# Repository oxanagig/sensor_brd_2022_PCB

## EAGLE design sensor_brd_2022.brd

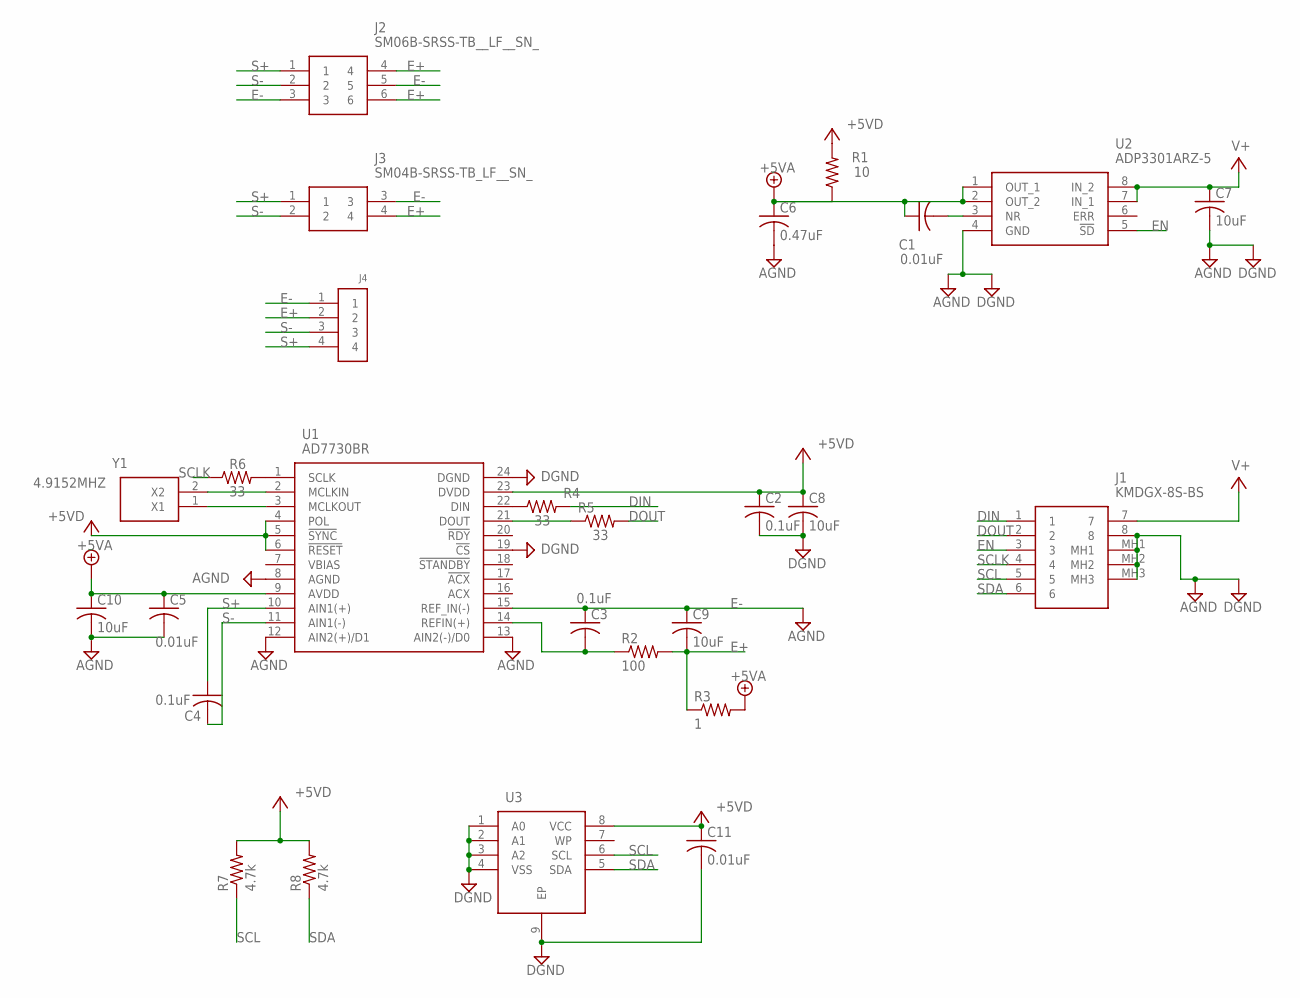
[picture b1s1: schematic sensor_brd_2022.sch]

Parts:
C1, C5, C11: 0.01uF; C0805K
C2, C3, C4: 0.1uF; C0805K
C6: 0.47uF; C1210
C7, C8, C9, C10: 10uF; C2012
J1: KMDGX-8S-BS; KMDGX8SBS
J2: SM06B-SRSS-TB__LF__SN_; SM06B-SRSS-TB
J3: SM04B-SRSS-TB_LF__SN_; SM04B-SRSS-TB(LFSN)
J4: 1X4-BIG; 1X04-BIG
R1: 10; R0603
R2: 100; R0603
R3: 1; R0603
R4, R5, R6: 33; R0603
R7, R8: 4.7k; R0603
U1: AD7730BR; SOIC127P1032X265-24N
U2: ADP3301ARZ-5; SOIC127P600X175-8N
U3: 24AA256-I_MF; SON127P600X500X100-9N; MANUFACTURER_PART_NUMBER 24LC256-I/MF
Y1: 4.9152MHz; 9C4000MAAJT; MANUFACTURER_PART_NUMBER ECS-049-20-5PXDN-TR; MOUSER_PART_NUMBER 520-049-20-5PXDN-TR

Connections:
+5V: C2.1, C8.1, C11.1, R1.2, R7.2, R8.2, U1.4 (POL), U1.5 (!SYNC), U1.6 (!RESET), U1.23 (DVDD), U3.8 (VCC)
+5V/1: C1.1, C5.1, C6.1, C10.1, R1.1, R3.2, U1.9 (AVDD), U2.1 (OUT_1), U2.2 (OUT_2)
AGND: C5.2, C6.2, C10.2, U1.8 (AGND), U1.12 (AIN2(+)/D1), U1.13 (AIN2(-)/D0)
DGND: C2.2, C7.2, C8.2, C11.2, J1.8, J1.MH1, J1.MH2, J1.MH3, U1.19 (!CS), U1.24 (DGND), U2.4 (GND), U3.1 (A0), U3.2 (A1), U3.3 (A2), U3.4 (VSS), U3.9 (EP)
DIN: J1.1, R4.2
DOUT: J1.2, R5.2
E+: C9.2, J2.4, J2.6, J3.4, J4.2, R2.2, R3.1
E-: C3.1, C9.1, J2.3, J2.5, J3.3, J4.1, U1.15 (REF_IN(-))
EN: J1.3, U2.5 (!SD)
unnamed: C1.2, U2.3 (NR)
unnamed: U1.2 (MCLKIN), Y1.2 (X2)
unnamed: U1.3 (MCLKOUT), Y1.1 (X1)
unnamed: R4.1, U1.22 (DIN)
unnamed: C3.2, R2.1, U1.14 (REFIN(+))
unnamed: R6.2, U1.1 (SCLK)
unnamed: R5.1, U1.21 (DOUT)
S+: C4.1, J2.1, J3.1, J4.4, U1.10 (AIN1(+))
S-: C4.2, J2.2, J3.2, J4.3, U1.11 (AIN1(-))
SCL: J1.5, R7.1, U3.6 (SCL)
SCLK: J1.4, R6.1
SDA: J1.6, R8.1, U3.5 (SDA)
V+: C7.1, J1.7, U2.7 (IN_1), U2.8 (IN_2)

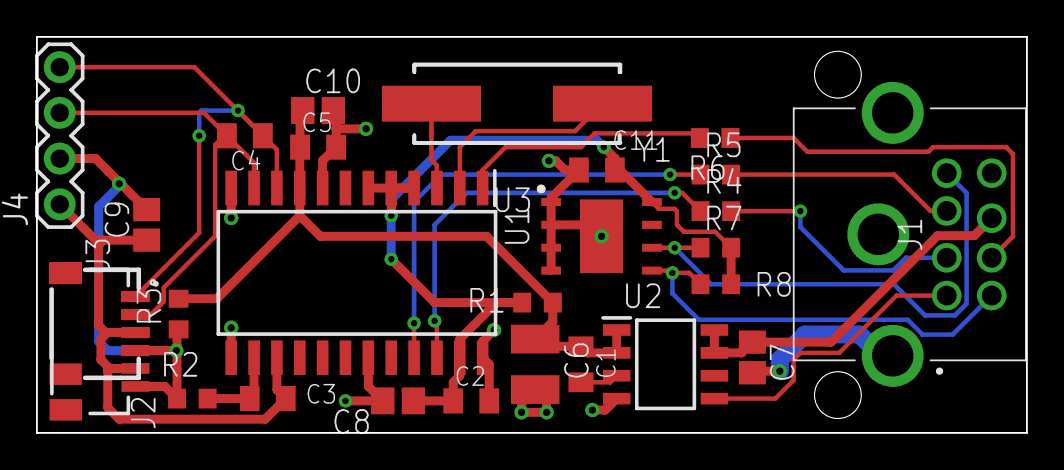
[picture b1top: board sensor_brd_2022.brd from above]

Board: 2 copper layers, 55.0 x 22.0 mm, 27 parts (0 on the bottom side), 22 nets.

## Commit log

2022-02-12 first commmit
2022-02-13 Create sensor_brd_2022.sch
    Initial commit for schematic
2022-02-14 brd file created
    -Changed the resistor from 0805 to 0603
    -Added brd file with initial components placment
2022-02-15 initial draft for layout
2022-02-16 First version send to JLCPCB
2022-02-16 Add version silkscreen
2022-05-08 Update the sch, added capacitor placement picture
2022-05-08 Removed unintentional commit
